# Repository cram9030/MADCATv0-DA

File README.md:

# MADCATv0-DA
Code base for MADCAT version 0 data aquisition

This project will be using the Beaglebone Black and LSM9DS1 sesnor. 

The code to interact with the LSM9DS1 was adapted from https://github.com/sparkfun/SparkFun_LSM9DS1_Arduino_Library

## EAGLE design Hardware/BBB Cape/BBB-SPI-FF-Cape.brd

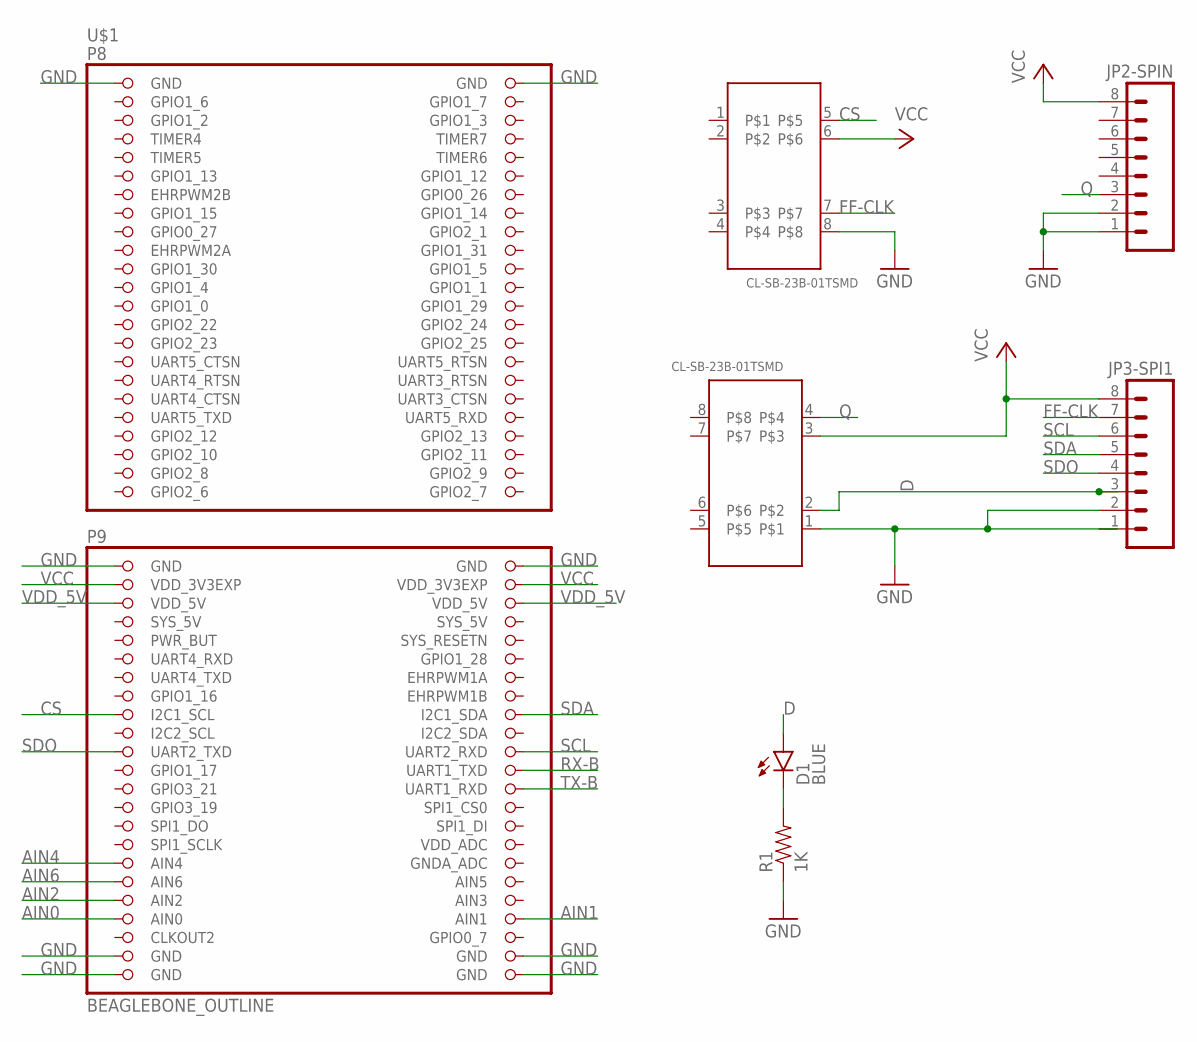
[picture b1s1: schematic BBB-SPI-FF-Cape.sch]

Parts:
D1: BLUE; LED-1206
JP2-SPIN, JP3-SPI1: M08BM08B-SRSS-TB; BM08B-SRSS-TB
R1: 1K; 1206
U$1: BEAGLEBONE_OUTLINE; BEAGLEBONE_SHIELD
U$2, U$3: CL-SB-23B-01TSMD; CL-SB-23B

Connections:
AIN0: U$1.85 (AIN0)
AIN1: U$1.86 (AIN1)
AIN2: U$1.83 (AIN2)
AIN4: U$1.79 (AIN4)
AIN6: U$1.81 (AIN6)
CS: U$1.63 (I2C1_SCL), U$2.5
D: D1.A, JP3-SPI1.3, U$3.2
FF-CLK: JP3-SPI1.7, U$2.7
GND: JP2-SPIN.1, JP2-SPIN.2, JP3-SPI1.2, R1.1, U$1.1 (GND), U$1.2 (GND), U$1.47 (GND), U$1.48 (GND), U$1.89 (GND), U$1.90 (GND), U$1.91 (GND), U$1.92 (GND), U$2.8, U$3.1
unnamed: D1.C, R1.2
Q: JP2-SPIN.3, U$3.4
RX-B: U$1.70 (UART1_TXD)
SCL: JP3-SPI1.6, U$1.68 (UART2_RXD)
SDA: JP3-SPI1.5, U$1.64 (I2C1_SDA)
SDO: JP3-SPI1.4, U$1.67 (UART2_TXD)
SYS_5V: U$1.53 (SYS_5V)
TX-B: U$1.72 (UART1_RXD)
VCC: JP2-SPIN.8, JP3-SPI1.8, U$1.49 (VDD_3V3EXP), U$1.50 (VDD_3V3EXP), U$2.6, U$3.3
VDD_5V: U$1.51 (VDD_5V), U$1.52 (VDD_5V)

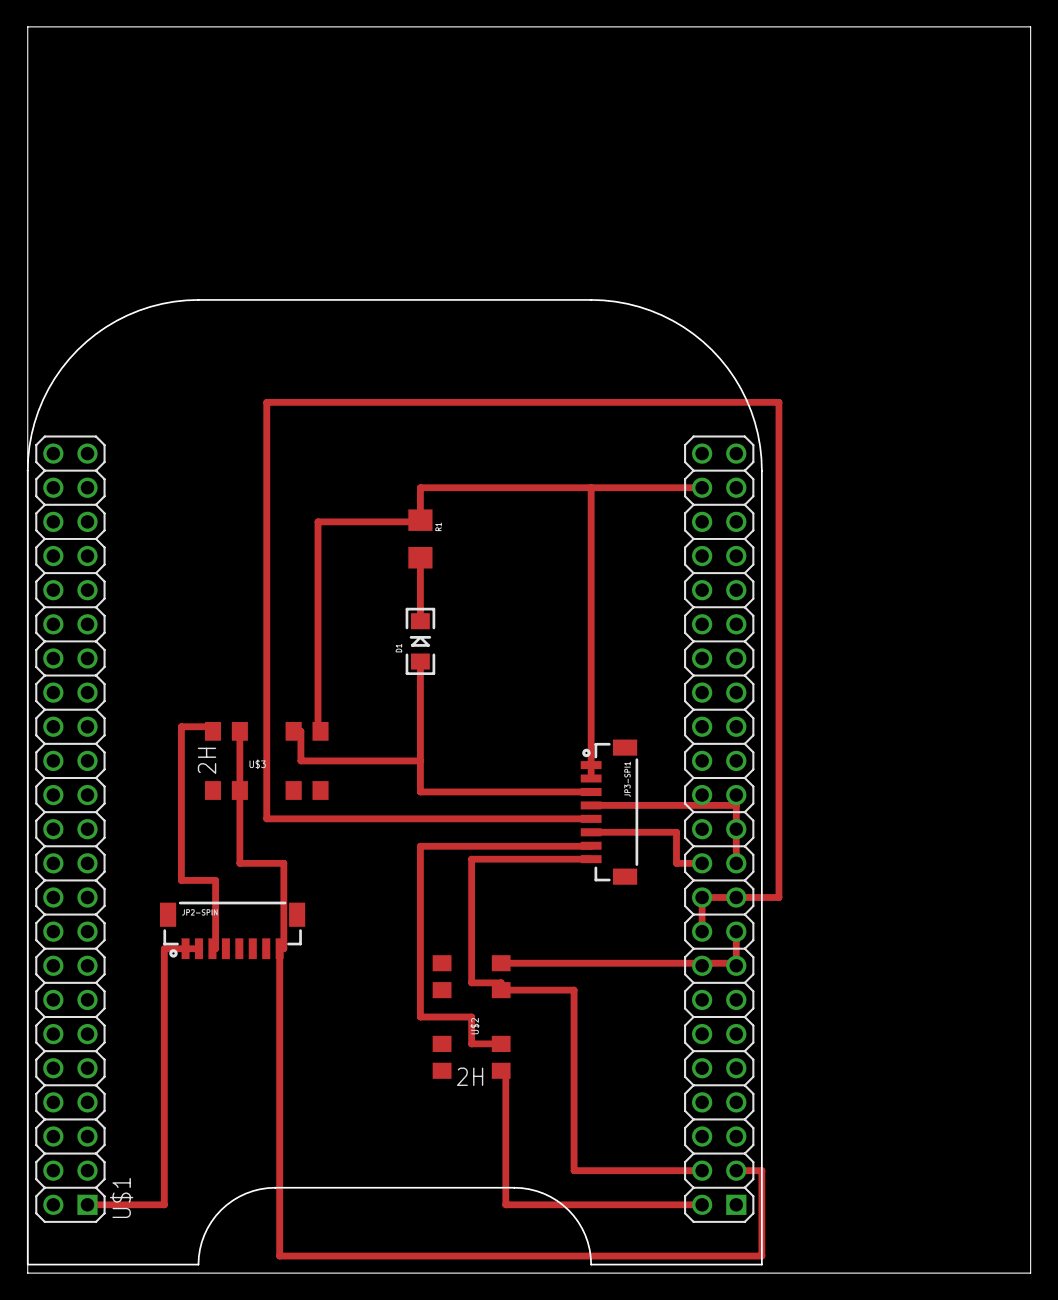
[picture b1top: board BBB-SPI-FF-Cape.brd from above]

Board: 2 copper layers, 74.6 x 92.7 mm, 7 parts (0 on the bottom side), 11 nets.

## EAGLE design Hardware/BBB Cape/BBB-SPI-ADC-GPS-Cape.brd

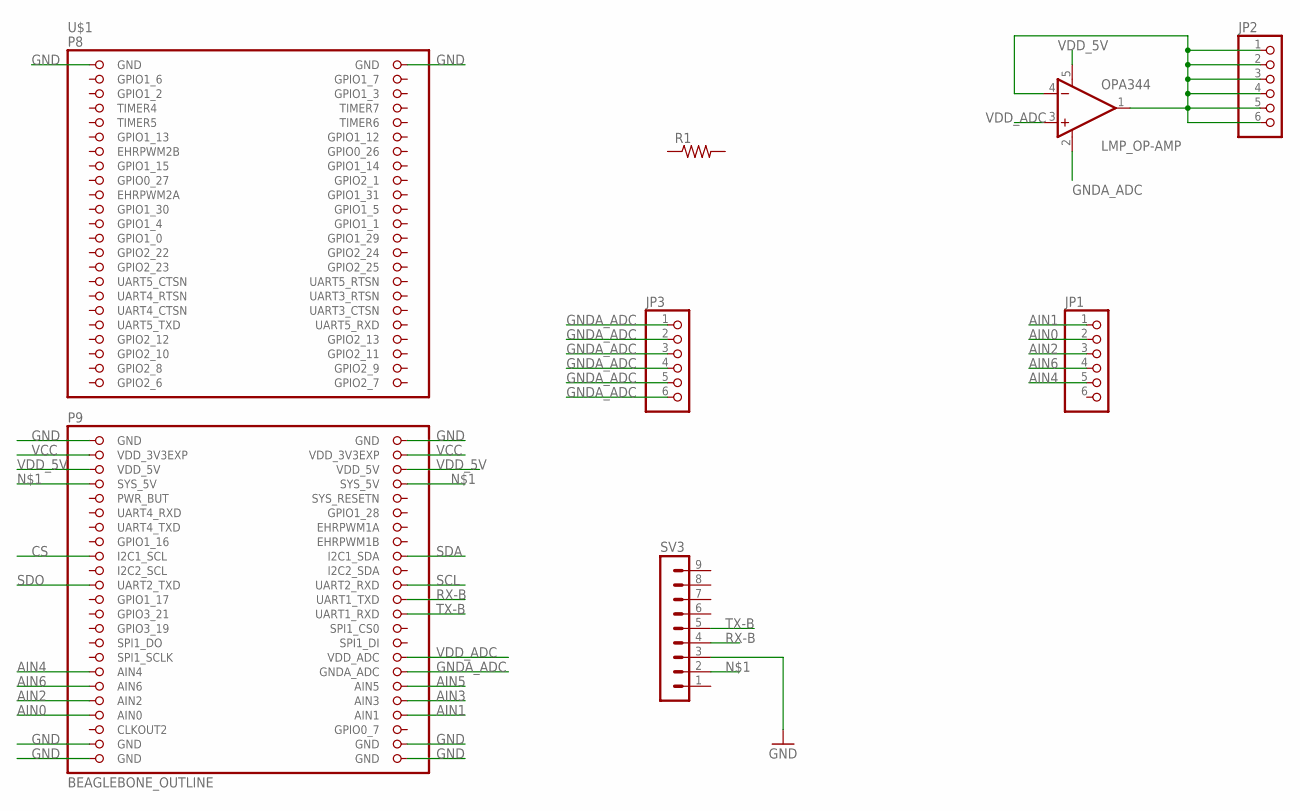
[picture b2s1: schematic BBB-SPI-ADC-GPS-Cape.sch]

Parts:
JP1, JP2, JP3: PINHD-1X6; 1X06
LMP_OP-AMP: OPA344; SOT23-5
R1: RES-US1206FAB; R1206FAB
SV3: MA09-1
U$1: BEAGLEBONE_OUTLINE; BEAGLEBONE_SHIELD

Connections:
AIN0: JP1.2, U$1.85 (AIN0)
AIN1: JP1.1, U$1.86 (AIN1)
AIN2: JP1.3, U$1.83 (AIN2)
AIN3: U$1.84 (AIN3)
AIN4: JP1.5, U$1.79 (AIN4)
AIN5: U$1.82 (AIN5)
AIN6: JP1.4, U$1.81 (AIN6)
CS: U$1.63 (I2C1_SCL)
GND: SV3.3, U$1.1 (GND), U$1.2 (GND), U$1.47 (GND), U$1.48 (GND), U$1.89 (GND), U$1.90 (GND), U$1.91 (GND), U$1.92 (GND)
GNDA_ADC: JP3.1, JP3.2, JP3.3, JP3.4, JP3.5, JP3.6, LMP_OP-AMP.2 (V-), U$1.80 (GNDA_ADC)
unnamed: SV3.2, U$1.53 (SYS_5V), U$1.54 (SYS_5V)
unnamed: JP2.1, JP2.2, JP2.3, JP2.4, JP2.5, JP2.6, LMP_OP-AMP.1 (OUT), LMP_OP-AMP.4 (-IN)
RX-B: SV3.4, U$1.70 (UART1_TXD)
SCL: U$1.68 (UART2_RXD)
SDA: U$1.64 (I2C1_SDA)
SDO: U$1.67 (UART2_TXD)
TX-B: SV3.5, U$1.72 (UART1_RXD)
VCC: U$1.49 (VDD_3V3EXP), U$1.50 (VDD_3V3EXP)
VDD_5V: LMP_OP-AMP.5 (V+), U$1.51 (VDD_5V), U$1.52 (VDD_5V)
VDD_ADC: LMP_OP-AMP.3 (+IN), U$1.78 (VDD_ADC)

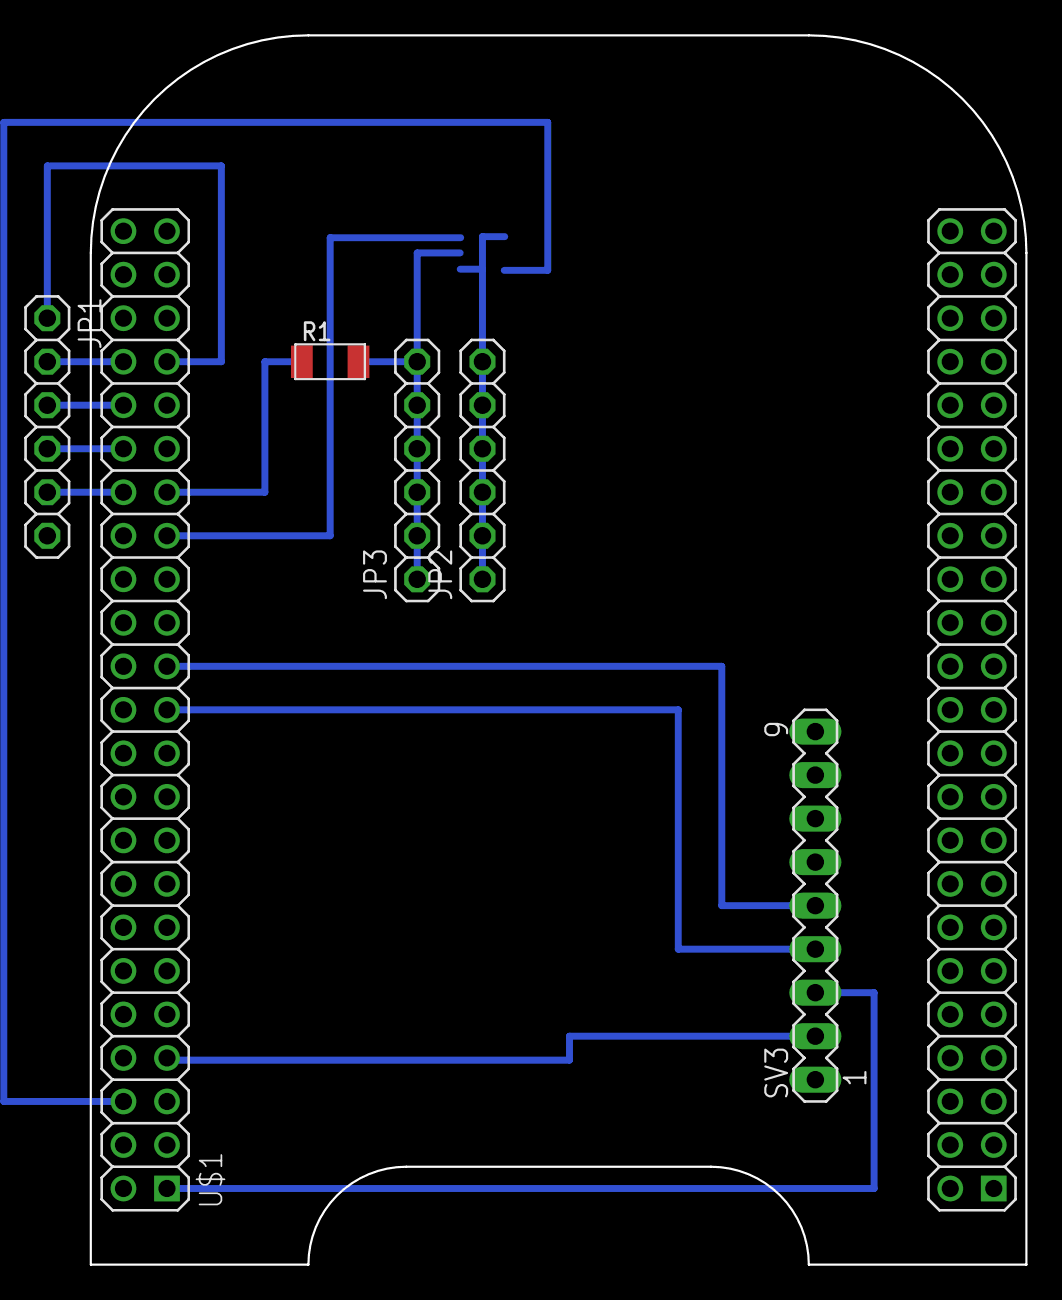
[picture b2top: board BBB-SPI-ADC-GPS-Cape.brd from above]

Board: 2 copper layers, 54.6 x 71.8 mm, 7 parts (1 on the bottom side), 14 nets.

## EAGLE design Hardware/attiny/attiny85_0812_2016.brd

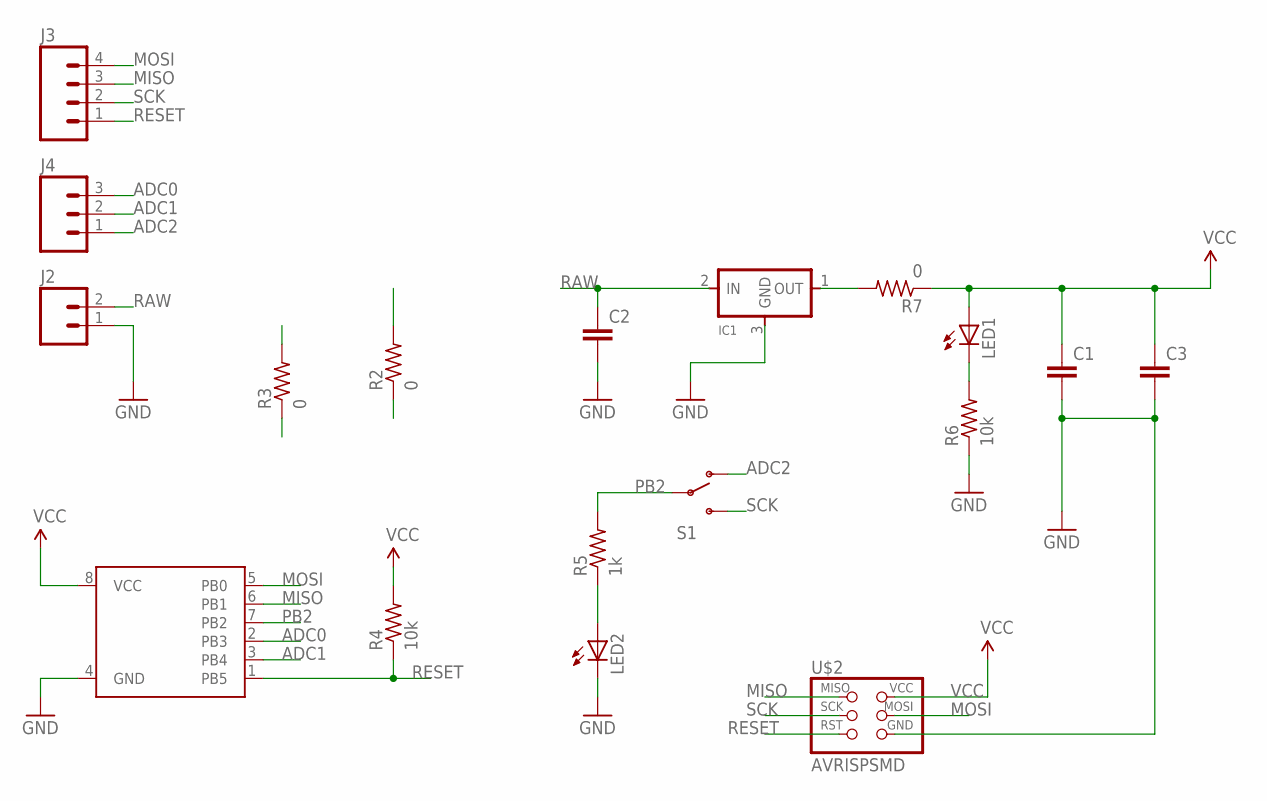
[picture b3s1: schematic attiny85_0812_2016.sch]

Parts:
C1, C2, C3: CAP1206; 1206
IC1: REGULATORSOT23; SOT23
J2: M02PTH; 1X02
J3: M04NO_SILK_ALL_ROUND; 1X04_NO_SILK_ALL_ROUND
J4: M03PTH; 1X03
LED1, LED2: LEDCHIPLED_1206; CHIPLED_1206
R2, R3, R7: 0; R1206FAB
R4, R6: 10k; R1206FAB
R5: 1k; R1206FAB
S1: SWITCH-SPDTPTH; SWITCH-SPDT
U$1: ATTINY85EIAJ; 8S2_EIAJ-85
U$2: AVRISPSMD; 2X03SMD

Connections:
ADC0: J4.3, U$1.2 (PB3)
ADC1: J4.2, U$1.3 (PB4)
ADC2: J4.1, S1.1 (O)
GND: C1.2, C2.2, C3.2, IC1.3 (GND), J2.1, LED2.C, R6.1, U$1.4 (GND), U$2.6 (GND)
MISO: J3.3, U$1.6 (PB1), U$2.1 (MISO)
MOSI: J3.4, R3.1, R3.2, U$1.5 (PB0), U$2.4 (MOSI)
unnamed: IC1.1 (OUT), R7.2
unnamed: LED1.C, R6.2
unnamed: LED2.A, R5.1
PB2: R5.2, S1.2, U$1.7 (PB2)
RAW: C2.1, IC1.2 (IN), J2.2
RESET: J3.1, R4.1, U$1.1 (PB5), U$2.5 (RST)
SCK: J3.2, S1.3 (S), U$2.3 (SCK)
VCC: C1.1, C3.1, LED1.A, R2.1, R2.2, R4.2, R7.1, U$1.8 (VCC), U$2.2 (VCC)

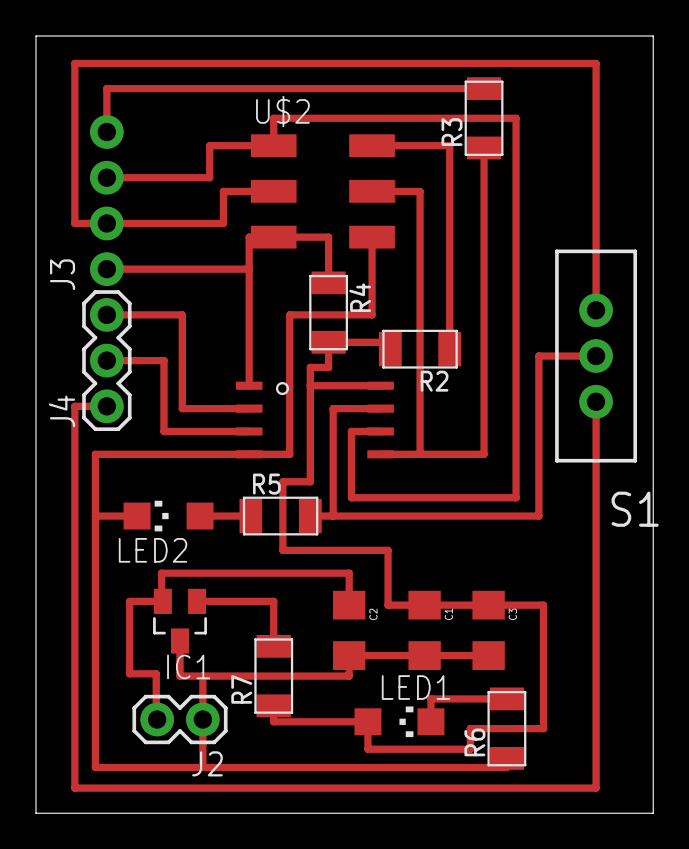
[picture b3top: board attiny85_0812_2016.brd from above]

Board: 2 copper layers, 34.3 x 43.2 mm, 18 parts (0 on the bottom side), 14 nets.

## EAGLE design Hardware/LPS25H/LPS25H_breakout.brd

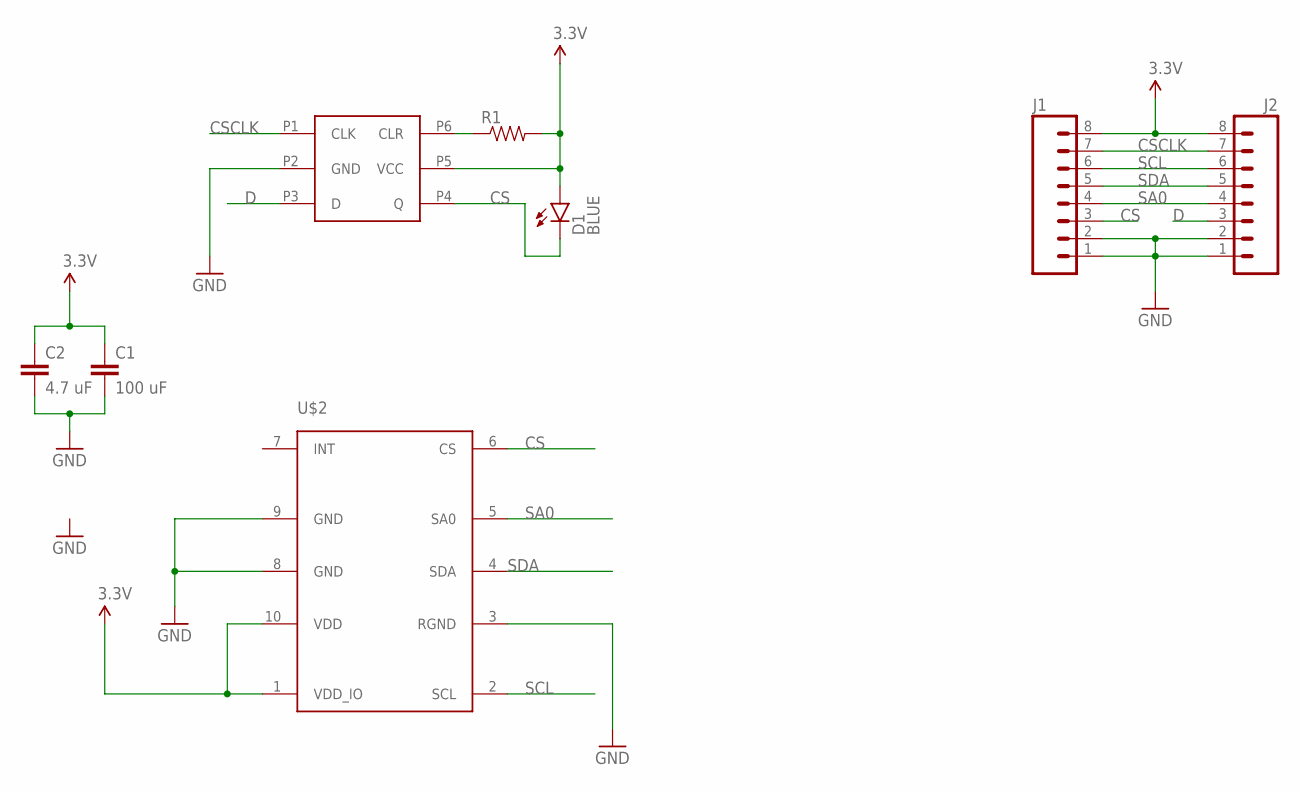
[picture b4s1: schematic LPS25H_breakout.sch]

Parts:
C1: 100 uF; 0603-CAP
C2: 4.7 uF; 0603-CAP
D1: BLUE; LED-0603
J1, J2: M08BM08B-SRSS-TB; BM08B-SRSS-TB
R1: RESISTOR0603-RES; 0603-RES
U$1: SN74LVC1G175
U$2: LPS25H

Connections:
3.3V: C1.1, C2.1, D1.A, J1.8, J2.8, R1.2, U$1.P5 (VCC), U$2.1 (VDD_IO), U$2.10 (VDD)
CS: D1.C, J1.3, U$1.P4 (Q), U$2.6 (CS)
CSCLK: J1.7, J2.7, U$1.P1 (CLK)
D: J2.3, U$1.P3 (D)
GND: C1.2, C2.2, J1.1, J1.2, J2.1, J2.2, U$1.P2 (GND), U$2.3 (RGND), U$2.8 (GND), U$2.9 (GND)
unnamed: R1.1, U$1.P6 (CLR)
SA0: J1.4, J2.4, U$2.5 (SA0)
SCL: J1.6, J2.6, U$2.2 (SCL)
SDA: J1.5, J2.5, U$2.4 (SDA)

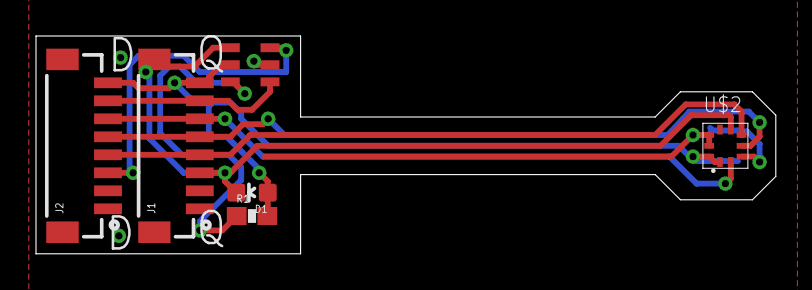
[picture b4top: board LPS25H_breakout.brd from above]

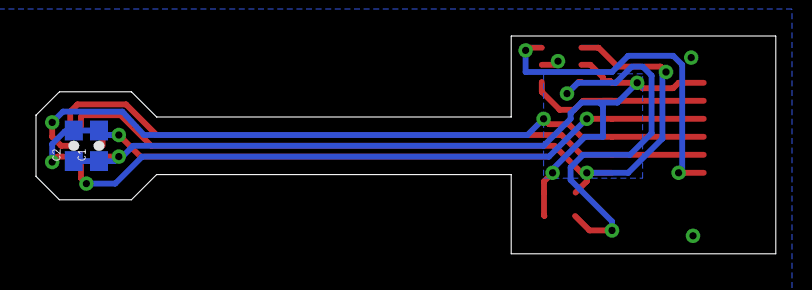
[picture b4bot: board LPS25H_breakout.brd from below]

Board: 2 copper layers, 41.1 x 12.1 mm, 8 parts (2 on the bottom side), 9 nets.

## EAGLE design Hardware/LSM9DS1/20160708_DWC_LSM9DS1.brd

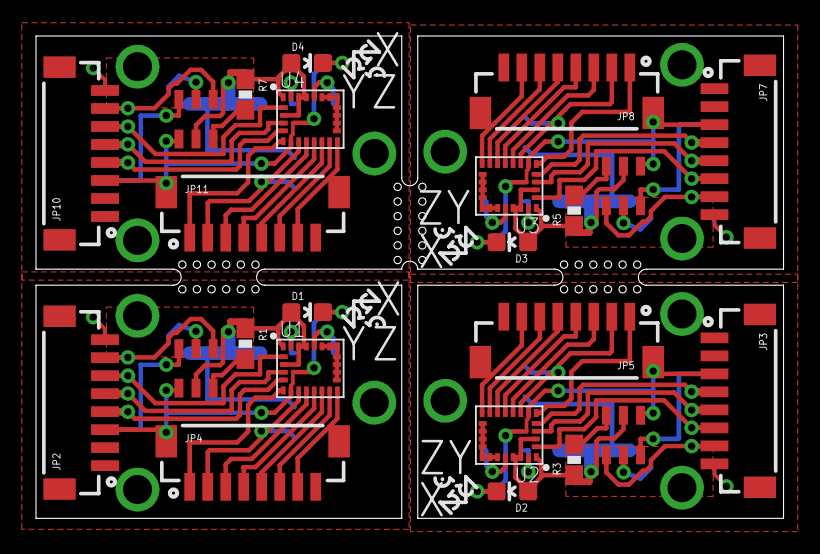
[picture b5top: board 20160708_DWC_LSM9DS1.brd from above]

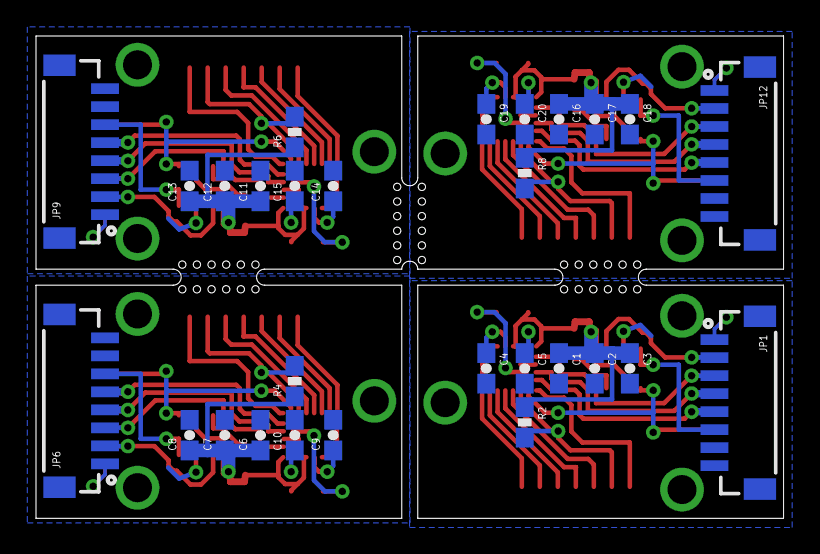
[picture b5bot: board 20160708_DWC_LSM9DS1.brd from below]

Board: 2 copper layers, 41.5 x 26.8 mm, 52 parts (28 on the bottom side), 72 nets.

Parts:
C1, C2, C5, C6, C7, C10, C11, C12, C15, C16, C17, C20: 0.1uF; 0603-CAP
C3, C8, C13, C18: 10uF; 0603-CAP
C4, C9, C14, C19: 10nF; 0603-CAP
D1, D2, D3, D4: BLUE; LED-0603
JP1, JP2, JP3, JP4, JP5, JP6, JP7, JP8, JP9, JP10, JP11, JP12: BM08B-SRSS-TB
R1, R2, R3, R4, R5, R6, R7, R8: 0603-RES
T1, T2, T3, T4: SN74LVC1G175
U1, U2, U3, U4: LSM9DS1; LGA24-8X4

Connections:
CSCLK: JP1.2, JP2.7, T1.P1
CSCLK1: JP3.7, JP6.2, T2.P1
CSCLK2: JP7.7, JP9.2, T3.P1
CSCLK3: JP10.7, JP12.2, T4.P1
CS_A/G: D1.C, JP2.3, T1.P4, U1.7
CS_A/G1: D2.C, JP3.3, T2.P4, U2.7
CS_A/G2: D3.C, JP7.3, T3.P4, U3.7
CS_A/G3: D4.C, JP10.3, T4.P4, U4.7
CS_M: JP4.2, R2.2, U1.8
CS_M1: JP5.2, R4.2, U2.8
CS_M2: JP8.2, R6.2, U3.8
CS_M3: JP11.2, R8.2, U4.8
D: JP1.6, T1.P3
D1: JP6.6, T2.P3
D2: JP9.6, T3.P3
D3: JP12.6, T4.P3
DEN_A/G: JP4.7, U1.13
DEN_A/G1: JP5.7, U2.13
DEN_A/G2: JP8.7, U3.13
DEN_A/G3: JP11.7, U4.13
DRDY_M: JP4.3, U1.9
DRDY_M1: JP5.3, U2.9
DRDY_M2: JP8.3, U3.9
DRDY_M3: JP11.3, U4.9
GND: C1.2, C2.2, C3.2, C4.2, C5.2, JP1.7, JP1.8, JP2.1, JP2.2, JP4.8, T1.P2, U1.14, U1.15, U1.16, U1.17, U1.18, U1.19, U1.20
GND1: C6.2, C7.2, C8.2, C9.2, C10.2, JP3.1, JP3.2, JP5.8, JP6.7, JP6.8, T2.P2, U2.14, U2.15, U2.16, U2.17, U2.18, U2.19, U2.20
GND2: C11.2, C12.2, C13.2, C14.2, C15.2, JP7.1, JP7.2, JP8.8, JP9.7, JP9.8, T3.P2, U3.14, U3.15, U3.16, U3.17, U3.18, U3.19, U3.20
GND3: C16.2, C17.2, C18.2, C19.2, C20.2, JP10.1, JP10.2, JP11.8, JP12.7, JP12.8, T4.P2, U4.14, U4.15, U4.16, U4.17, U4.18, U4.19, U4.20
INT1_A/G: JP4.5, U1.11
INT1_A/G1: JP5.5, U2.11
INT1_A/G2: JP8.5, U3.11
INT1_A/G3: JP11.5, U4.11
INT2_A/G: JP4.6, U1.12
INT2_A/G1: JP5.6, U2.12
INT2_A/G2: JP8.6, U3.12
INT2_A/G3: JP11.6, U4.12
INT_M: JP4.4, U1.10
INT_M1: JP5.4, U2.10
INT_M2: JP8.4, U3.10
INT_M3: JP11.4, U4.10
unnamed: R1.2, T1.P6
unnamed: C4.1, U1.21
unnamed: C5.1, U1.24
unnamed: C9.1, U2.21
unnamed: C10.1, U2.24
unnamed: R3.2, T2.P6
unnamed: C14.1, U3.21
unnamed: C15.1, U3.24
unnamed: R5.2, T3.P6
unnamed: C19.1, U4.21
unnamed: C20.1, U4.24
unnamed: R7.2, T4.P6
SCL: JP1.3, JP2.6, U1.2
SCL1: JP3.6, JP6.3, U2.2
SCL2: JP7.6, JP9.3, U3.2
SCL3: JP10.6, JP12.3, U4.2
SDA: JP1.4, JP2.5, U1.4
SDA1: JP3.5, JP6.4, U2.4
SDA2: JP7.5, JP9.4, U3.4
SDA3: JP10.5, JP12.4, U4.4
SDO_A/G: JP1.5, JP2.4, U1.5
SDO_A/G1: JP3.4, JP6.5, U2.5
SDO_A/G2: JP7.4, JP9.5, U3.5
SDO_A/G3: JP10.4, JP12.5, U4.5
SDO_M: JP4.1, U1.6
SDO_M1: JP5.1, U2.6
SDO_M2: JP8.1, U3.6
SDO_M3: JP11.1, U4.6
VDD: C1.1, C2.1, C3.1, D1.A, JP1.1, JP2.8, R1.1, R2.1, T1.P5, U1.1, U1.3, U1.22, U1.23
VDD1: C6.1, C7.1, C8.1, D2.A, JP3.8, JP6.1, R3.1, R4.1, T2.P5, U2.1, U2.3, U2.22, U2.23
VDD2: C11.1, C12.1, C13.1, D3.A, JP7.8, JP9.1, R5.1, R6.1, T3.P5, U3.1, U3.3, U3.22, U3.23
VDD3: C16.1, C17.1, C18.1, D4.A, JP10.8, JP12.1, R7.1, R8.1, T4.P5, U4.1, U4.3, U4.22, U4.23

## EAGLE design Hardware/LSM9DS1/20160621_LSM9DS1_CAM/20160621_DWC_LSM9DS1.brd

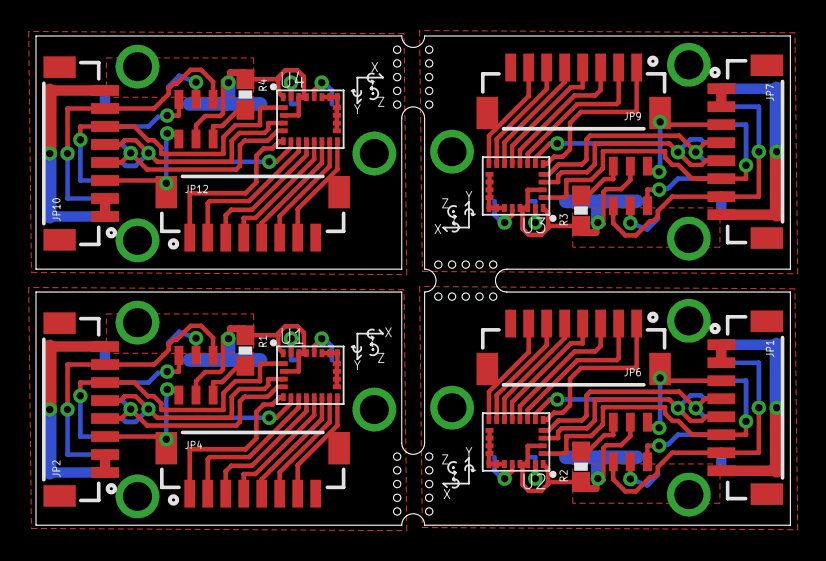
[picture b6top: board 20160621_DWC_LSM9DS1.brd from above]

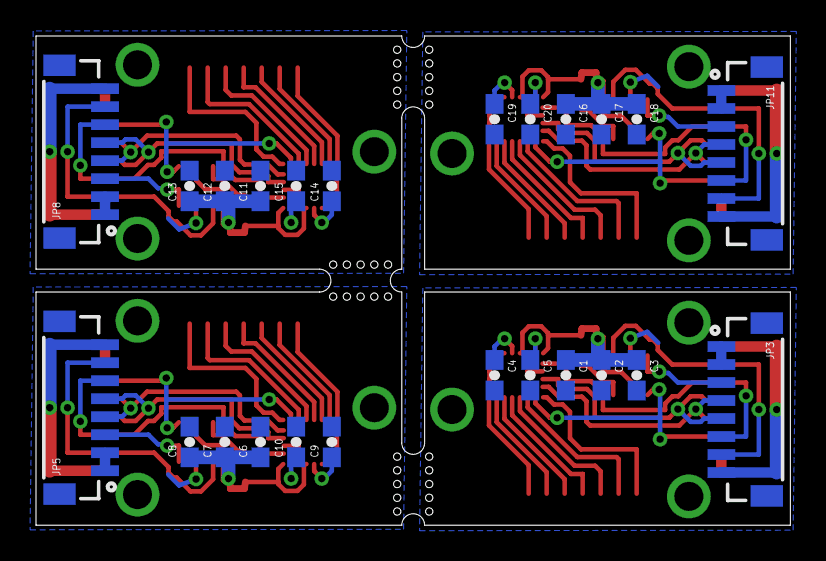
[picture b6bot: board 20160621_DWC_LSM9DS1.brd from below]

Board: 2 copper layers, 41.9 x 27.2 mm, 44 parts (24 on the bottom side), 72 nets.

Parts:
C1, C2, C5, C6, C7, C10, C11, C12, C15, C16, C17, C20: 0.1uF; 0603-CAP
C3, C8, C13, C18: 10uF; 0603-CAP
C4, C9, C14, C19: 10nF; 0603-CAP
JP1, JP2, JP3, JP4, JP5, JP6, JP7, JP8, JP9, JP10, JP11, JP12: BM08B-SRSS-TB
R1, R2, R3, R4: 0603-RES
U1, U2, U3, U4: LSM9DS1; LGA24-8X4
U$1, U$2, U$3, U$4: SN74LVC1G175

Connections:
CSCLK: JP2.7, JP3.7, U$1.P1
CSCLK1: JP1.7, JP5.7, U$2.P1
CSCLK2: JP7.7, JP8.7, U$3.P1
CSCLK3: JP10.7, JP11.7, U$4.P1
CS_A/G: JP2.3, U1.7, U$1.P4
CS_A/G1: JP1.3, U2.7, U$2.P4
CS_A/G2: JP7.3, U3.7, U$3.P4
CS_A/G3: JP10.3, U4.7, U$4.P4
CS_M: JP4.2, U1.8
CS_M1: JP6.2, U2.8
CS_M2: JP9.2, U3.8
CS_M3: JP12.2, U4.8
D: JP3.3, U$1.P3
D1: JP5.3, U$2.P3
D2: JP8.3, U$3.P3
D3: JP11.3, U$4.P3
DEN_A/G: JP4.7, U1.13
DEN_A/G1: JP6.7, U2.13
DEN_A/G2: JP9.7, U3.13
DEN_A/G3: JP12.7, U4.13
DRDY_M: JP4.3, U1.9
DRDY_M1: JP6.3, U2.9
DRDY_M2: JP9.3, U3.9
DRDY_M3: JP12.3, U4.9
GND: C1.2, C2.2, C3.2, C4.2, C5.2, JP2.1, JP2.2, JP3.1, JP3.2, JP4.8, U1.14, U1.15, U1.16, U1.17, U1.18, U1.19, U1.20, U$1.P2
GND1: C6.2, C7.2, C8.2, C9.2, C10.2, JP1.1, JP1.2, JP5.1, JP5.2, JP6.8, U2.14, U2.15, U2.16, U2.17, U2.18, U2.19, U2.20, U$2.P2
GND2: C11.2, C12.2, C13.2, C14.2, C15.2, JP7.1, JP7.2, JP8.1, JP8.2, JP9.8, U3.14, U3.15, U3.16, U3.17, U3.18, U3.19, U3.20, U$3.P2
GND3: C16.2, C17.2, C18.2, C19.2, C20.2, JP10.1, JP10.2, JP11.1, JP11.2, JP12.8, U4.14, U4.15, U4.16, U4.17, U4.18, U4.19, U4.20, U$4.P2
INT1_A/G: JP4.5, U1.11
INT1_A/G1: JP6.5, U2.11
INT1_A/G2: JP9.5, U3.11
INT1_A/G3: JP12.5, U4.11
INT2_A/G: JP4.6, U1.12
INT2_A/G1: JP6.6, U2.12
INT2_A/G2: JP9.6, U3.12
INT2_A/G3: JP12.6, U4.12
INT_M: JP4.4, U1.10
INT_M1: JP6.4, U2.10
INT_M2: JP9.4, U3.10
INT_M3: JP12.4, U4.10
unnamed: R1.2, U$1.P6
unnamed: C4.1, U1.21
unnamed: C5.1, U1.24
unnamed: C9.1, U2.21
unnamed: C10.1, U2.24
unnamed: R2.2, U$2.P6
unnamed: C14.1, U3.21
unnamed: C15.1, U3.24
unnamed: R3.2, U$3.P6
unnamed: C19.1, U4.21
unnamed: C20.1, U4.24
unnamed: R4.2, U$4.P6
SCL: JP2.6, JP3.6, U1.2
SCL1: JP1.6, JP5.6, U2.2
SCL2: JP7.6, JP8.6, U3.2
SCL3: JP10.6, JP11.6, U4.2
SDA: JP2.5, JP3.5, U1.4
SDA1: JP1.5, JP5.5, U2.4
SDA2: JP7.5, JP8.5, U3.4
SDA3: JP10.5, JP11.5, U4.4
SDO_A/G: JP2.4, JP3.4, U1.5
SDO_A/G1: JP1.4, JP5.4, U2.5
SDO_A/G2: JP7.4, JP8.4, U3.5
SDO_A/G3: JP10.4, JP11.4, U4.5
SDO_M: JP4.1, U1.6
SDO_M1: JP6.1, U2.6
SDO_M2: JP9.1, U3.6
SDO_M3: JP12.1, U4.6
VDD: C1.1, C2.1, C3.1, JP2.8, JP3.8, R1.1, U1.1, U1.3, U1.22, U1.23, U$1.P5
VDD1: C6.1, C7.1, C8.1, JP1.8, JP5.8, R2.1, U2.1, U2.3, U2.22, U2.23, U$2.P5
VDD2: C11.1, C12.1, C13.1, JP7.8, JP8.8, R3.1, U3.1, U3.3, U3.22, U3.23, U$3.P5
VDD3: C16.1, C17.1, C18.1, JP10.8, JP11.8, R4.1, U4.1, U4.3, U4.22, U4.23, U$4.P5

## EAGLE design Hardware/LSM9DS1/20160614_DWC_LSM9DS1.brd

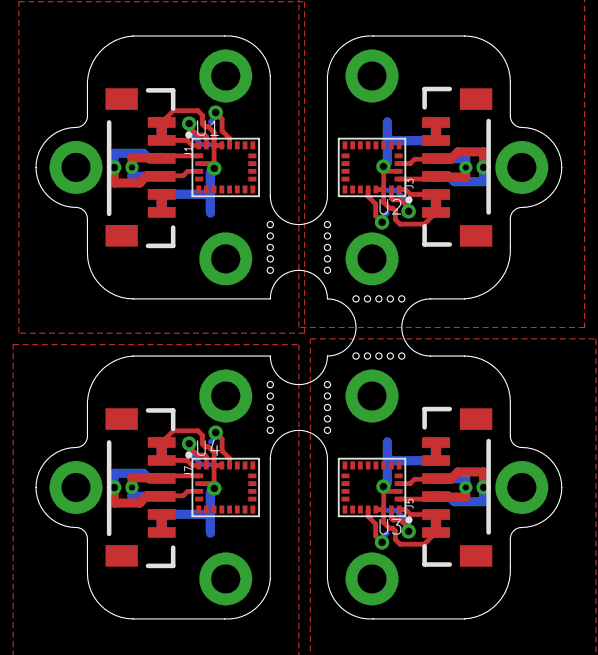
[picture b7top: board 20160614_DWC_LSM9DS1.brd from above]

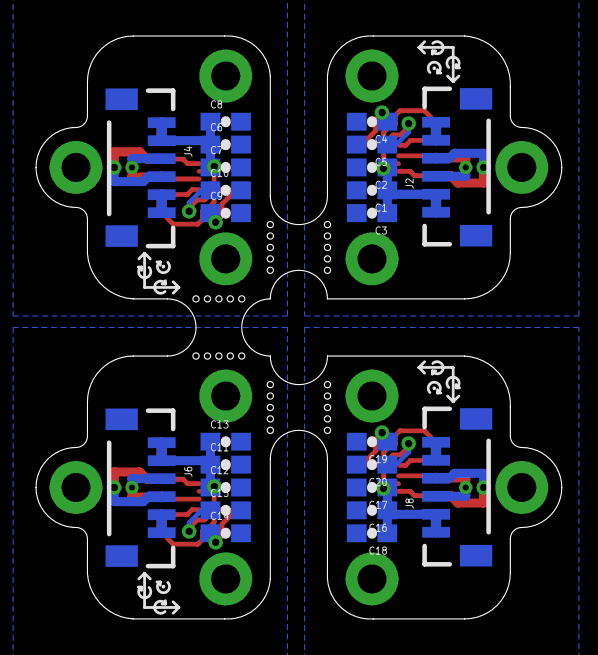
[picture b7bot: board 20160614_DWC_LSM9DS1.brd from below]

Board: 2 copper layers, 29.2 x 32.4 mm, 32 parts (24 on the bottom side), 24 nets.

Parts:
C1, C2, C5, C6, C7, C10, C11, C12, C15, C16, C17, C20: 0.1uF; 0603-CAP
C3, C8, C13, C18: 10uF; 0603-CAP
C4, C9, C14, C19: 10nF; 0603-CAP
J1, J2, J3, J4, J5, J6, J7, J8: 1X06-1MM
U1, U2, U3, U4: LSM9DS1; LGA24-8X4

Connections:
GND: C1.2, C2.2, C3.2, C4.2, C5.2, J1.5, J1.6, J2.5, J2.6, U1.14, U1.15, U1.16, U1.17, U1.18, U1.19, U1.20
GND1: C6.2, C7.2, C8.2, C9.2, C10.2, J3.5, J3.6, J4.5, J4.6, U2.14, U2.15, U2.16, U2.17, U2.18, U2.19, U2.20
GND2: C11.2, C12.2, C13.2, C14.2, C15.2, J5.5, J5.6, J6.5, J6.6, U3.14, U3.15, U3.16, U3.17, U3.18, U3.19, U3.20
GND3: C16.2, C17.2, C18.2, C19.2, C20.2, J7.5, J7.6, J8.5, J8.6, U4.14, U4.15, U4.16, U4.17, U4.18, U4.19, U4.20
unnamed: C9.1, U2.21
unnamed: C4.1, U1.21
unnamed: C5.1, U1.24
unnamed: C10.1, U2.24
unnamed: C14.1, U3.21
unnamed: C15.1, U3.24
unnamed: C19.1, U4.21
unnamed: C20.1, U4.24
SCL: J1.3, J2.3, U1.2
SCL1: J3.3, J4.3, U2.2
SCL2: J5.3, J6.3, U3.2
SCL3: J7.3, J8.3, U4.2
SDA: J1.4, J2.4, U1.4
SDA1: J3.4, J4.4, U2.4
SDA2: J5.4, J6.4, U3.4
SDA3: J7.4, J8.4, U4.4
VDD: C1.1, C2.1, C3.1, J1.1, J1.2, J2.1, J2.2, U1.1, U1.3, U1.22, U1.23
VDD1: C6.1, C7.1, C8.1, J3.1, J3.2, J4.1, J4.2, U2.1, U2.3, U2.22, U2.23
VDD2: C11.1, C12.1, C13.1, J5.1, J5.2, J6.1, J6.2, U3.1, U3.3, U3.22, U3.23
VDD3: C16.1, C17.1, C18.1, J7.1, J7.2, J8.1, J8.2, U4.1, U4.3, U4.22, U4.23

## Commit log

2016-06-14 :lollipop: Added .gitattributes & .gitignore files
2016-06-15 Initial commit
    These files in the include are meant to communicate to the LSM9DS1
    sensor and are based off the code from
    https://github.com/sparkfun/SparkFun_LSM9DS1_Arduino_Library
    This has not been compiled or tested in any way yet
2016-06-16 Added test file
    Everything compiles but the test outputs the same wrong values everytime
2016-06-17 Single testing is working
2016-06-20 Updated I2CreadBytes
    It now reads multiple bytes at a time
2016-06-20 Created reading 2 axis accel and gyro reading functions
    This increases the read time of two axis if the two axis being accessed
    are in adjacent registers
2016-06-21 added spi library
2016-06-21 implemented spi
2016-06-21 changed test to test spi
2016-06-21 Deleted who am I print
2016-06-21 it compiles
2016-06-22 Corrected the bus address SPI now initialized
2016-06-23 SPI communication is working now
    SPI mode is 0 and the chip select pin for the Mag needs to be tied high
2016-06-23 Updated SPI Speed
2016-06-23 Trying to get SPIreadBytes to work
    printing data shows that they are all the same
2016-06-24 Commiting to revert
2016-06-24 Revert "Updated SPI Speed"
    This reverts commit 54cf3980477879e2225a32491cb75498a3efa604.
2016-06-24 commit to revert
2016-06-24 SPI read is working now
    Though gravity is 1/3 what it should be. This still needs to be
    addressed
2016-06-24 Added Hardware folder and software folder
2016-06-24 Actually added hardware folder
2016-06-24 uncommented while(1)
2016-06-24 Corrected the SpiDevice.h files
2016-06-25 added flip flop code
2016-06-28 updated test code
2016-06-28 Commiting to branch
2016-06-28 Updated and fixed Spi communications
    The issues mostly arose from the fact that initMag() was still running
    even when the Mag was disabled resulting in the Accel registers getting
    reset
2016-06-28 Fixed table
2016-06-28 Unbolding pin line
2016-06-28 Added P9 header
2016-06-28 Formatting
2016-06-28 added second imu.begin()
2016-06-29 added some initialization for the flip flops. Still doesn't work
2016-06-29 More formating
2016-06-29 test code without gpio
2016-06-30 added separate if statements for initializing imus
2016-07-01 added 4th imu
2016-07-01 sampling with 4 imus
2016-07-06 BeagleBone Black Shield and Board
2016-07-07 Complete routing for cape
    Also updated the schematic just calling out the ground connections
2016-07-07 Updated switch lay out and routing
2016-07-08 tests 7 sensors now reading both the accel and gyro from each. Data is saved in testing.txt
2016-07-09 Rev 3 IMU Board
    Here it is, in all its glory.
2016-07-09 Added Indicator LED
2016-07-09 Corrected Position for GPS headers
2016-07-11 updated trace widths on cape
2016-07-11 created the images for the modela
2016-07-11 Added CAM Files
2016-07-12 Fixed the headers for the M08 cables coming from the IMU
2016-07-12 Cleaned up some of the traces
2016-07-12 updated cam
2016-07-13 added gps code
2016-07-13 created png for updated cape
2016-07-15 Split cape into two components
    Lower layer is the GPS and Pot and upper layer is the SPI connections
2016-07-16 added mk1 LPS25H hardware
2016-07-19 hot, warm, and cold start code for gps
2016-07-19 Added High Sensitivity Mode for the GPS
2016-07-20 LPS25H MK II
2016-07-22 Commit for merge
2016-07-24 added cam info (for a flex order)
2016-08-09 Added code for APA with BBB bit banging
    This code has not even been compiled yet. First push for revert
    purposes.
2016-08-10 it's been a while since my last commit but this is the tiny board eagle files
2016-08-10 Updated APA protocol so now everything compiles
    THIS HAS NOT BEEN TESTED YET
    compile command for BBB
    g++ -pthread Include/GPIO.cpp Include/BBBDigitialIOAPA.cpp
    Include/APAProtocol.cpp test/APABBBtest.cpp -o APABBtest -w
2016-08-15 Small changes - commit just to checkout other branch
2016-08-22 APABBtest.cpp compiles
    I am still unsure if I want to remove the protocol class and just make
    it an library and a data structure. I think that will be better but this
    commit is to just have refrence of the class structure.
2016-08-23 APA still not working
    For some reason the GPIO class does not seem to be working correctly
    once intialized outside the intialization function. I am suspending work
    on this and focusing on the reading the analog values. This reqires
    recreating the analog cape.
2016-08-30 Added GPS test
    It works!
2016-08-30 i think this is just the final version of the tiny but there might be more, it's been a while since I commited
2016-08-30 git told me to commit
2016-08-30 created images for mill for bbb cape
2016-09-02 working version of the adc/gps cape
2016-09-07 many iterations of the spi-ff cape
2016-09-07 you'll never guess, more updates to the cape!
2016-09-16 Quick update to power budget
2016-11-16 Added ADC codes and spi device tree
2016-11-21 Testing reading of the string pots
2016-11-22 Flight Test Compiles
2016-11-23 Updated Flight test slightly
    Just added simple commandline functionality
2016-11-24 Final update for flight testing on 11/23/2016
2016-12-22 V1 Skin Sensor
2016-12-22 Fixed pour issues
2016-12-27 Added sensor and cleaned up the board
2017-01-04 Modular skin sensor (mk 2, rigid board)
2017-02-15 Added calibration code

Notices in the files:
parts and their libraries:
SparkFun-AnalogIC: Licensing:Creative Commons ShareAlike 4.0 International - https://creativecommons.org/licenses/by-sa/4.0
